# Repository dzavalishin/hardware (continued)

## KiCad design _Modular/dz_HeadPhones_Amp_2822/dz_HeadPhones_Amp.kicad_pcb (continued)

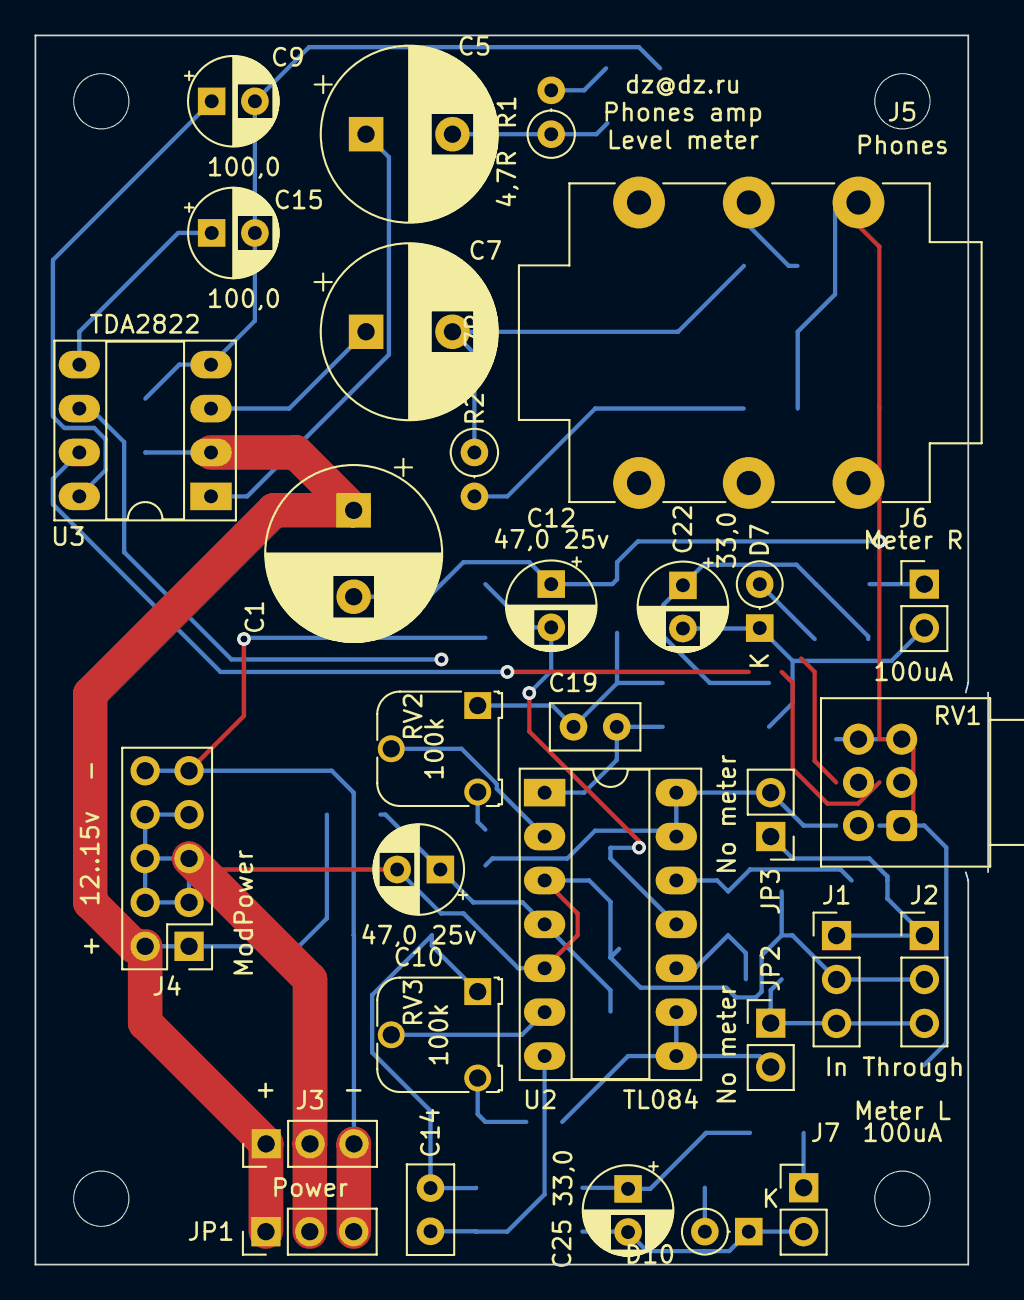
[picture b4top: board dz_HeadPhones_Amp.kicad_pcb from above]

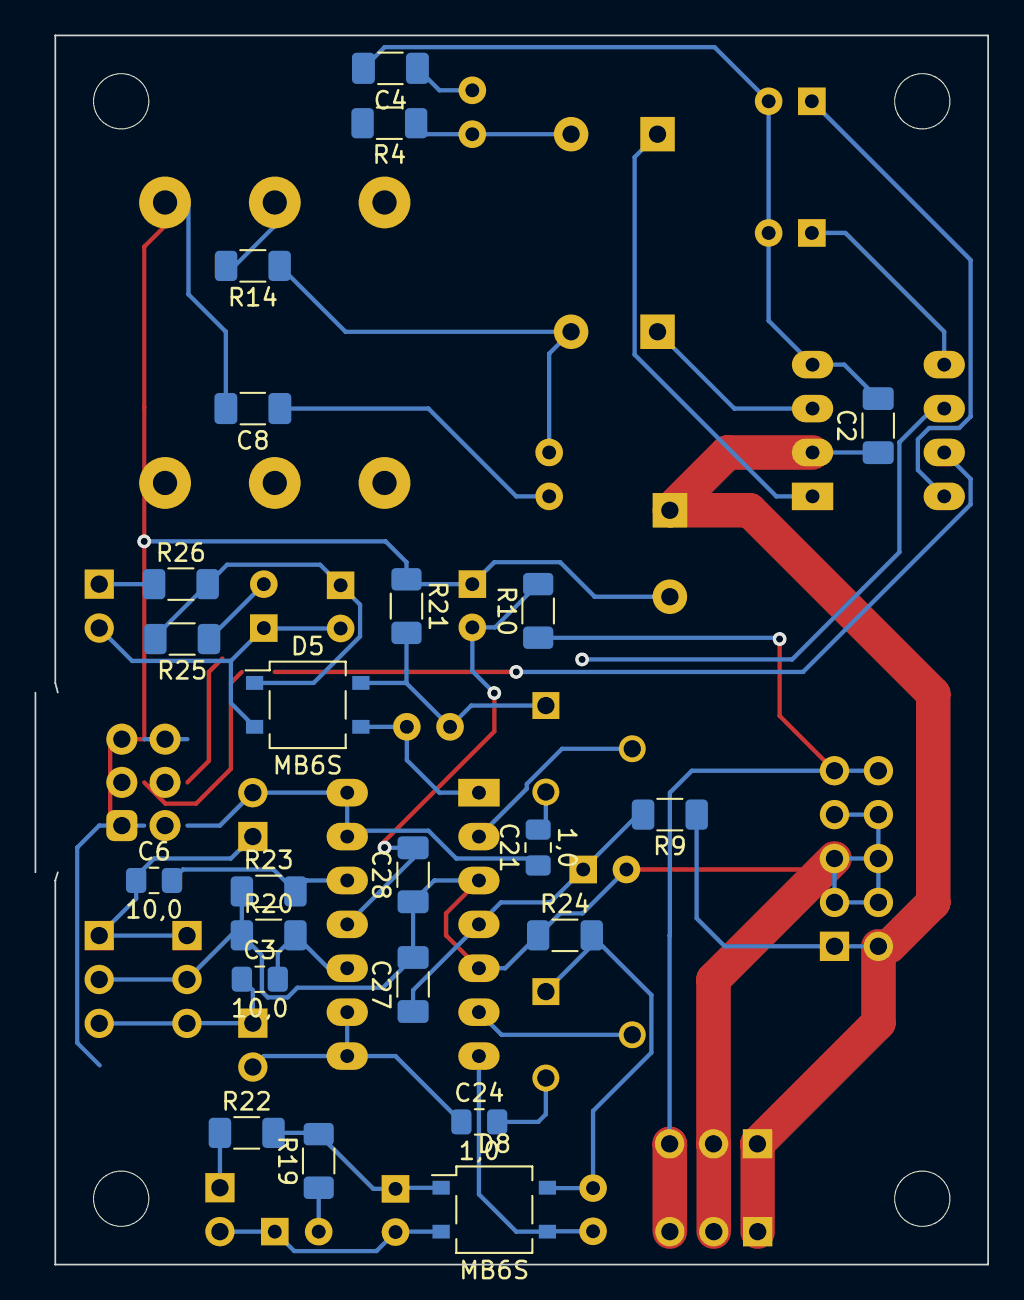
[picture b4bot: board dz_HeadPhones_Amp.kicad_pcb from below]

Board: 2 copper layers, 55.1 x 71.1 mm, 57 parts (23 on the bottom side), 39 nets.

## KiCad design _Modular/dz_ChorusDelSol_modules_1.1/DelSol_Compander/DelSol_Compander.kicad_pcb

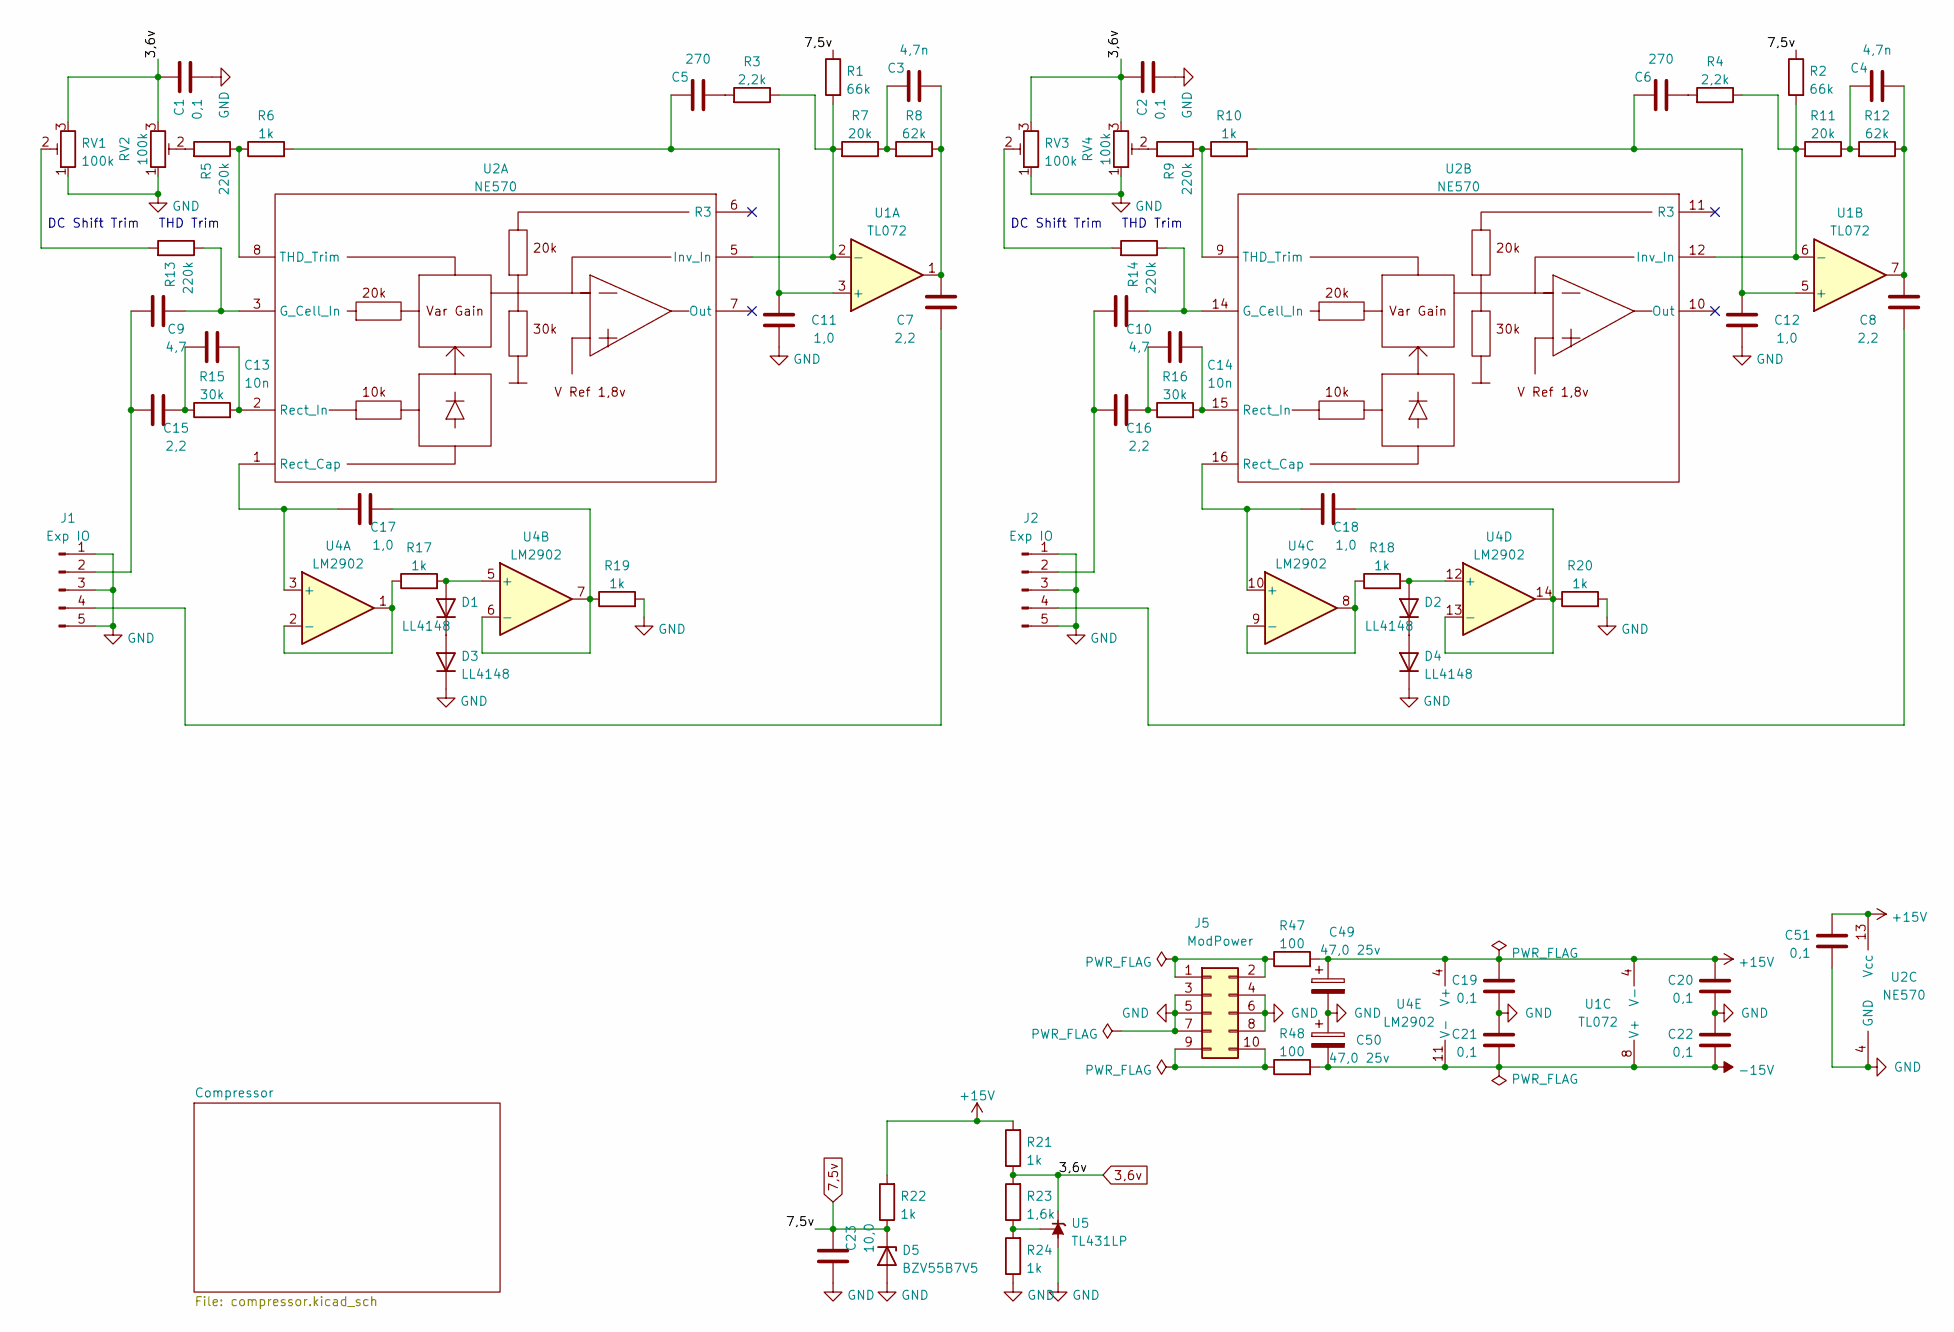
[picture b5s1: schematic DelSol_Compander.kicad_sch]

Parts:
C1, C2, C19, C20, C21, C22, C51: 0,1; C_1206_3216Metric_Pad1.33x1.80mm_HandSolder
C3, C4: 4,7n; C_0805_2012Metric_Pad1.18x1.45mm_HandSolder
C5, C6: 270; C_0805_2012Metric_Pad1.18x1.45mm_HandSolder
C7, C8, C15, C16: 2,2; C_0805_2012Metric_Pad1.18x1.45mm_HandSolder
C9, C10: 4,7; C_0805_2012Metric_Pad1.18x1.45mm_HandSolder
C11, C12, C17, C18: 1,0; C_0805_2012Metric_Pad1.18x1.45mm_HandSolder
C13, C14: 10n; C_0805_2012Metric_Pad1.18x1.45mm_HandSolder
C23: 10,0; C_0805_2012Metric_Pad1.18x1.45mm_HandSolder
C49, C50: 47,0 25v; CP_Radial_D5.0mm_P2.50mm
D1, D2, D3, D4: LL4148; D_MiniMELF
D5: BZV55B7V5; D_MiniMELF
J1, J2: Exp IO; JST_EH_B5B-EH-A_1x05_P2.50mm_Vertical
J5: ModPower; PinHeader_2x05_P2.54mm_Vertical
R1, R2: 66k; R_1206_3216Metric_Pad1.30x1.75mm_HandSolder
R3, R4: 2,2k; R_1206_3216Metric_Pad1.30x1.75mm_HandSolder
R5, R9, R13, R14: 220k; R_1206_3216Metric_Pad1.30x1.75mm_HandSolder
R6, R10, R17, R18, R19, R20, R21, R22, R24: 1k; R_1206_3216Metric_Pad1.30x1.75mm_HandSolder
R7, R11: 20k; R_1206_3216Metric_Pad1.30x1.75mm_HandSolder
R8, R12: 62k; R_1206_3216Metric_Pad1.30x1.75mm_HandSolder
R15, R16: 30k; R_1206_3216Metric_Pad1.30x1.75mm_HandSolder
R23: 1,6k; R_1206_3216Metric_Pad1.30x1.75mm_HandSolder
R47, R48: 100; R_1206_3216Metric_Pad1.30x1.75mm_HandSolder
RV1, RV2, RV3, RV4: 100k; Potentiometer_Runtron_RM-065_Vertical
U1: TL072; DIP-8_W7.62mm
U2: NE570; DIP-16_W7.62mm_Socket_LongPads
U4: LM2902; DIP-14_W7.62mm_Socket_LongPads
U5: TL431LP; TO-92_Inline

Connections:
3,6v: C1.2, C2.2, R21.1, R23.2, RV1.3, RV2.3, RV3.3, RV4.3, U5.3 (K); also elsewhere on the board
7,5v: C23.2, D5.1 (K), R1.1, R2.1, R22.1; also elsewhere on the board
+15V: C19.2, C20.2, C49.1, C51.2, R21.2, R22.2, R47.2, U1.4 (V-), U2.13 (Vcc), U4.4 (V+); also elsewhere on the board
-15V: C21.1, C22.1, C50.2, R48.2, U1.8 (V+), U4.11 (V-); also elsewhere on the board
GND: C1.1, C2.1, C11.1, C12.1, C19.1, C20.1, C21.2, C22.2, C23.1, C49.2, C50.1, C51.1, D3.1 (K), D4.1 (K), D5.2 (A), J1.1, J1.3, J1.5, J2.1, J2.3, J2.5, J5.3, J5.4, J5.5, J5.6, J5.7, J5.8, R19.2, R20.2, R24.1, RV1.1, RV2.1, RV3.1, RV4.1, U2.4 (GND), U5.2 (A); also elsewhere on the board
unnamed: C3.1, C7.2, R8.1, U1.1
unnamed: C3.2, R7.1, R8.2
unnamed: C4.1, C8.2, R12.1, U1.7
unnamed: C4.2, R11.1, R12.2
unnamed: C5.1, R3.2
unnamed: C6.1, R4.2
unnamed: C7.1, J1.4
unnamed: C8.1, J2.4
unnamed: C9.2, R13.1, U2.3 (G_Cell_In)
unnamed: C10.1, C16.1, J2.2
unnamed: C10.2, R14.1, U2.14 (G_Cell_In)
unnamed: C5.2, C11.2, R6.2, U1.3 (+)
unnamed: C6.2, C12.2, R10.2, U1.5 (+)
unnamed: C13.1, C15.2, R15.1
unnamed: C13.2, R15.2, U2.2 (Rect_In)
unnamed: C14.1, C16.2, R16.1
unnamed: C14.2, R16.2, U2.15 (Rect_In)
unnamed: C9.1, C15.1, J1.2
unnamed: C17.1, U2.1 (Rect_Cap), U4.3 (+)
unnamed: C17.2, R19.1, U4.6 (-), U4.7
unnamed: C18.1, U2.16 (Rect_Cap), U4.10 (+)
unnamed: C18.2, R20.1, U4.13 (-), U4.14
unnamed: D1.1 (K), D3.2 (A)
unnamed: D1.2 (A), R17.2, U4.5 (+)
unnamed: D2.1 (K), D4.2 (A)
unnamed: D2.2 (A), R18.2, U4.12 (+)
unnamed: J5.1, J5.2, R47.1
unnamed: J5.9, J5.10, R48.1
unnamed: R1.2, R3.1, R7.2, U1.2 (-), U2.5 (Inv_In)
unnamed: R5.1, R6.1, U2.8 (THD_Trim)
unnamed: R5.2, RV2.2
unnamed: R9.2, RV4.2
unnamed: R9.1, R10.1, U2.9 (THD_Trim)
unnamed: R2.2, R4.1, R11.2, U1.6 (-), U2.12 (Inv_In)
unnamed: R13.2, RV1.2
unnamed: R14.2, RV3.2
unnamed: R17.1, U4.1, U4.2 (-)
unnamed: R18.1, U4.8, U4.9 (-)
unnamed: R23.1, R24.2, U5.1 (REF)

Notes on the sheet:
THD Trim
DC Shift Trim

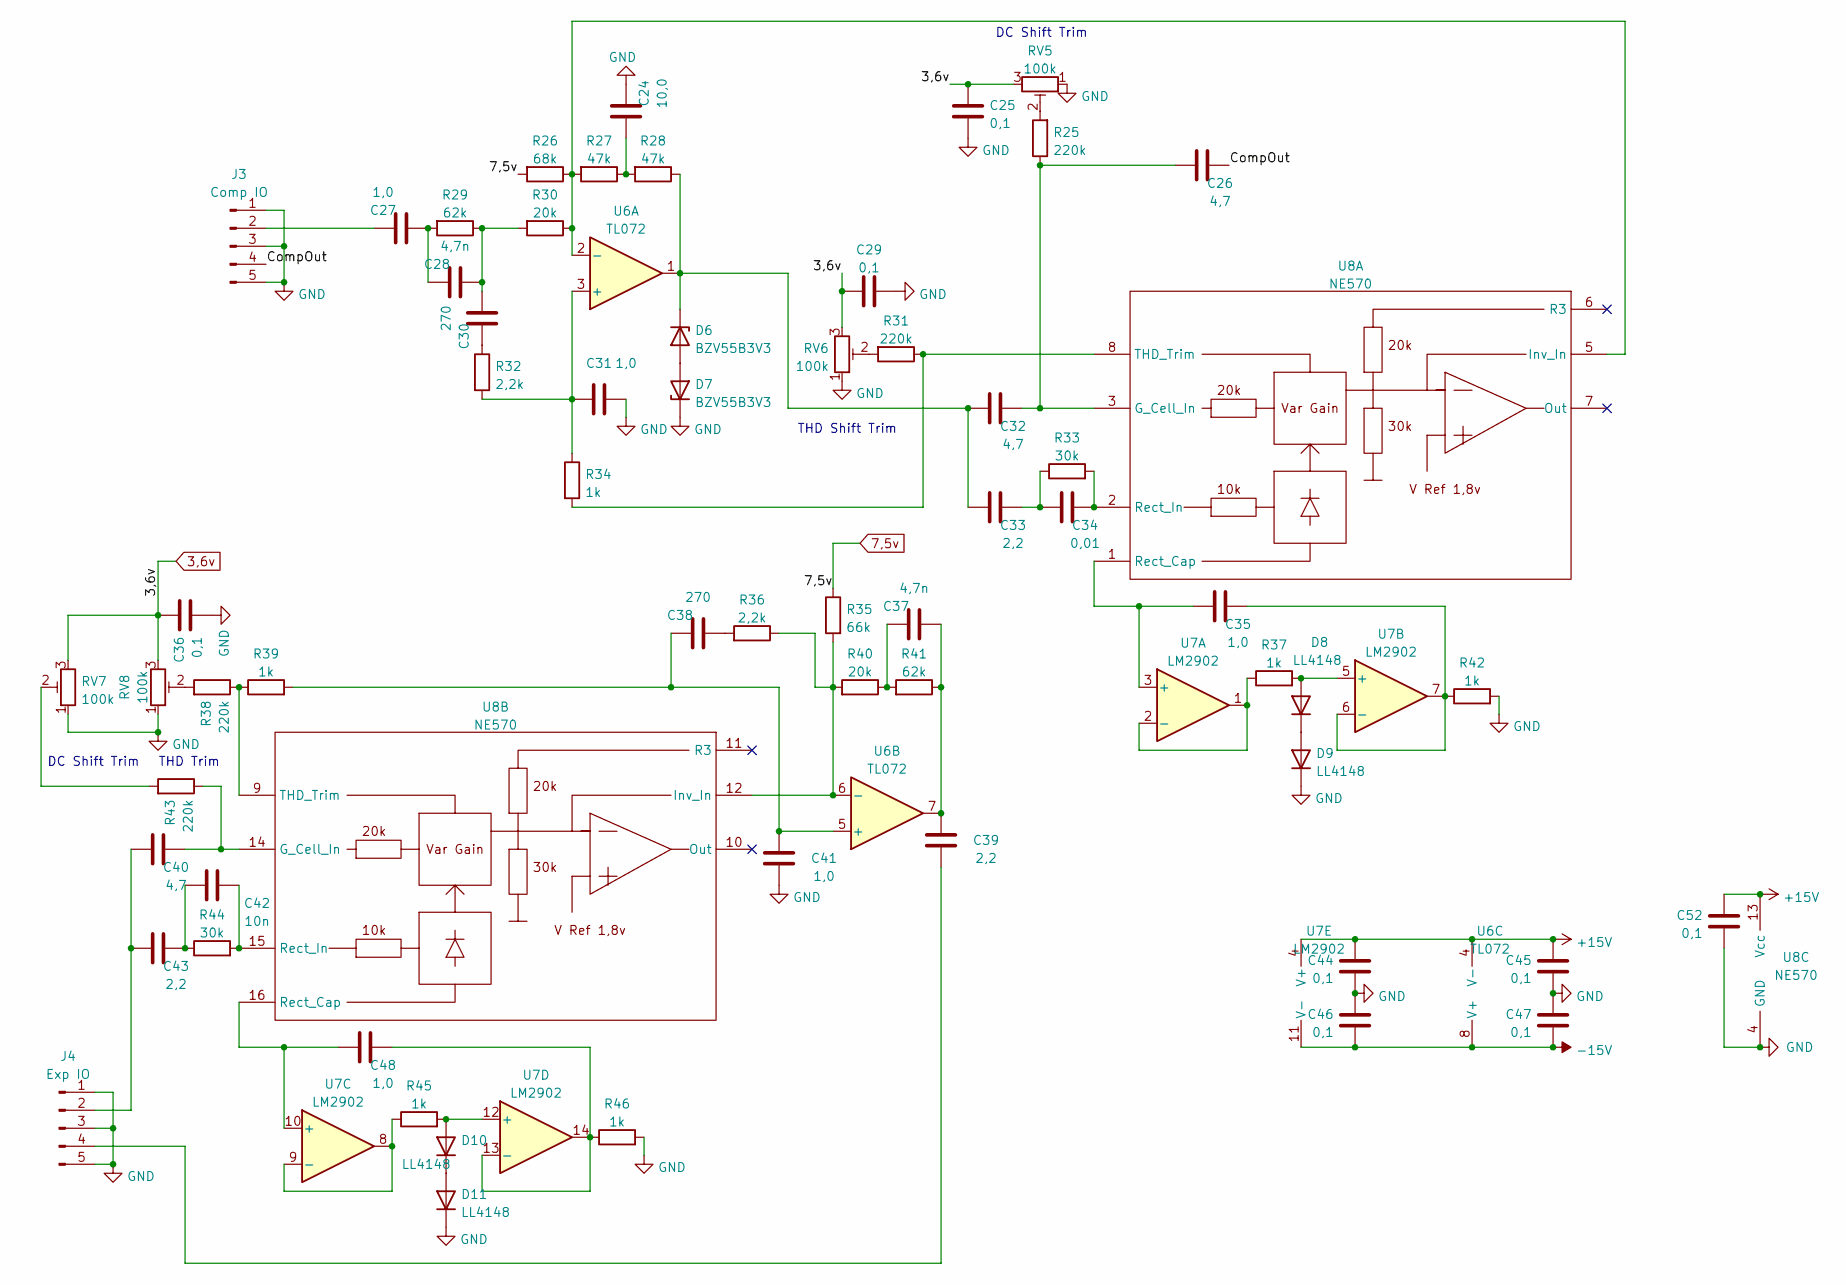
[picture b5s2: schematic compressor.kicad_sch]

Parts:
C24: 10,0; C_0805_2012Metric_Pad1.18x1.45mm_HandSolder
C25, C29, C36, C44, C45, C46, C47, C52: 0,1; C_1206_3216Metric_Pad1.33x1.80mm_HandSolder
C26, C32, C40: 4,7; C_0805_2012Metric_Pad1.18x1.45mm_HandSolder
C27, C31, C35, C41, C48: 1,0; C_0805_2012Metric_Pad1.18x1.45mm_HandSolder
C28, C37: 4,7n; C_0805_2012Metric_Pad1.18x1.45mm_HandSolder
C30, C38: 270; C_0805_2012Metric_Pad1.18x1.45mm_HandSolder
C33, C39, C43: 2,2; C_0805_2012Metric_Pad1.18x1.45mm_HandSolder
C34: 0,01; C_0805_2012Metric_Pad1.18x1.45mm_HandSolder
C42: 10n; C_0805_2012Metric_Pad1.18x1.45mm_HandSolder
D6, D7: BZV55B3V3; D_MiniMELF
D8, D9, D10, D11: LL4148; D_MiniMELF
J3: Comp IO; JST_EH_B5B-EH-A_1x05_P2.50mm_Vertical
J4: Exp IO; JST_EH_B5B-EH-A_1x05_P2.50mm_Vertical
R25, R31, R38, R43: 220k; R_1206_3216Metric_Pad1.30x1.75mm_HandSolder
R26: 68k; R_1206_3216Metric_Pad1.30x1.75mm_HandSolder
R27, R28: 47k; R_1206_3216Metric_Pad1.30x1.75mm_HandSolder
R29, R41: 62k; R_1206_3216Metric_Pad1.30x1.75mm_HandSolder
R30, R40: 20k; R_1206_3216Metric_Pad1.30x1.75mm_HandSolder
R32, R36: 2,2k; R_1206_3216Metric_Pad1.30x1.75mm_HandSolder
R33, R44: 30k; R_1206_3216Metric_Pad1.30x1.75mm_HandSolder
R34, R37, R39, R42, R45, R46: 1k; R_1206_3216Metric_Pad1.30x1.75mm_HandSolder
R35: 66k; R_1206_3216Metric_Pad1.30x1.75mm_HandSolder
RV5, RV6, RV7, RV8: 100k; Potentiometer_Runtron_RM-065_Vertical
U6: TL072; DIP-8_W7.62mm
U7: LM2902; DIP-14_W7.62mm_Socket_LongPads
U8: NE570; DIP-16_W7.62mm_Socket_LongPads

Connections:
3,6v: C25.2, C29.1, C36.2, RV5.3, RV6.3, RV7.3, RV8.3; also elsewhere on the board
7,5v: R26.2, R35.1; also elsewhere on the board
+15V: C44.2, C45.2, C52.2, U6.4 (V-), U7.4 (V+), U8.13 (Vcc); also elsewhere on the board
-15V: C46.1, C47.1, U6.8 (V+), U7.11 (V-); also elsewhere on the board
/Compressor/CompOut: C26.2, J3.4
GND: C24.2, C25.1, C29.2, C31.2, C36.1, C41.1, C44.1, C45.1, C46.2, C47.2, C52.1, D7.1 (K), D9.1 (K), D11.1 (K), J3.1, J3.3, J3.5, J4.1, J4.3, J4.5, R42.2, R46.2, RV5.1, RV6.1, RV7.1, RV8.1, U8.4 (GND); also elsewhere on the board
unnamed: C24.1, R27.1, R28.2
unnamed: C26.1, C32.2, R25.1, U8.3 (G_Cell_In)
unnamed: C27.1, C28.2, R29.2
unnamed: C27.2, J3.2
unnamed: C28.1, C30.1, R29.1, R30.2
unnamed: C30.2, R32.1
unnamed: C31.1, R32.2, R34.1, U6.3 (+)
unnamed: C32.1, C33.1, D6.1 (K), R28.1, U6.1
unnamed: C33.2, C34.1, R33.1
unnamed: C34.2, R33.2, U8.2 (Rect_In)
unnamed: C35.1, U7.3 (+), U8.1 (Rect_Cap)
unnamed: C35.2, R42.1, U7.6 (-), U7.7
unnamed: C37.1, C39.2, R41.1, U6.7
unnamed: C37.2, R40.1, R41.2
unnamed: C38.1, R36.2
unnamed: C38.2, C41.2, R39.2, U6.5 (+)
unnamed: C39.1, J4.4
unnamed: C40.1, C43.1, J4.2
unnamed: C40.2, R43.1, U8.14 (G_Cell_In)
unnamed: C42.1, C43.2, R44.1
unnamed: C42.2, R44.2, U8.15 (Rect_In)
unnamed: C48.1, U7.10 (+), U8.16 (Rect_Cap)
unnamed: C48.2, R46.1, U7.13 (-), U7.14
unnamed: D6.2 (A), D7.2 (A)
unnamed: D8.1 (K), D9.2 (A)
unnamed: D8.2 (A), R37.2, U7.5 (+)
unnamed: D10.1 (K), D11.2 (A)
unnamed: D10.2 (A), R45.2, U7.12 (+)
unnamed: R25.2, RV5.2
unnamed: R26.1, R27.2, R30.1, U6.2 (-), U8.5 (Inv_In)
unnamed: R31.1, R34.2, U8.8 (THD_Trim)
unnamed: R31.2, RV6.2
unnamed: R35.2, R36.1, R40.2, U6.6 (-), U8.12 (Inv_In)
unnamed: R37.1, U7.1, U7.2 (-)
unnamed: R38.1, R39.1, U8.9 (THD_Trim)
unnamed: R38.2, RV8.2
unnamed: R43.2, RV7.2
unnamed: R45.1, U7.8, U7.9 (-)

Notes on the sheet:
DC Shift Trim
THD Shift Trim
THD Trim

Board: 2 copper layers, 131 parts (109 on the bottom side), 83 nets, no tracks yet.

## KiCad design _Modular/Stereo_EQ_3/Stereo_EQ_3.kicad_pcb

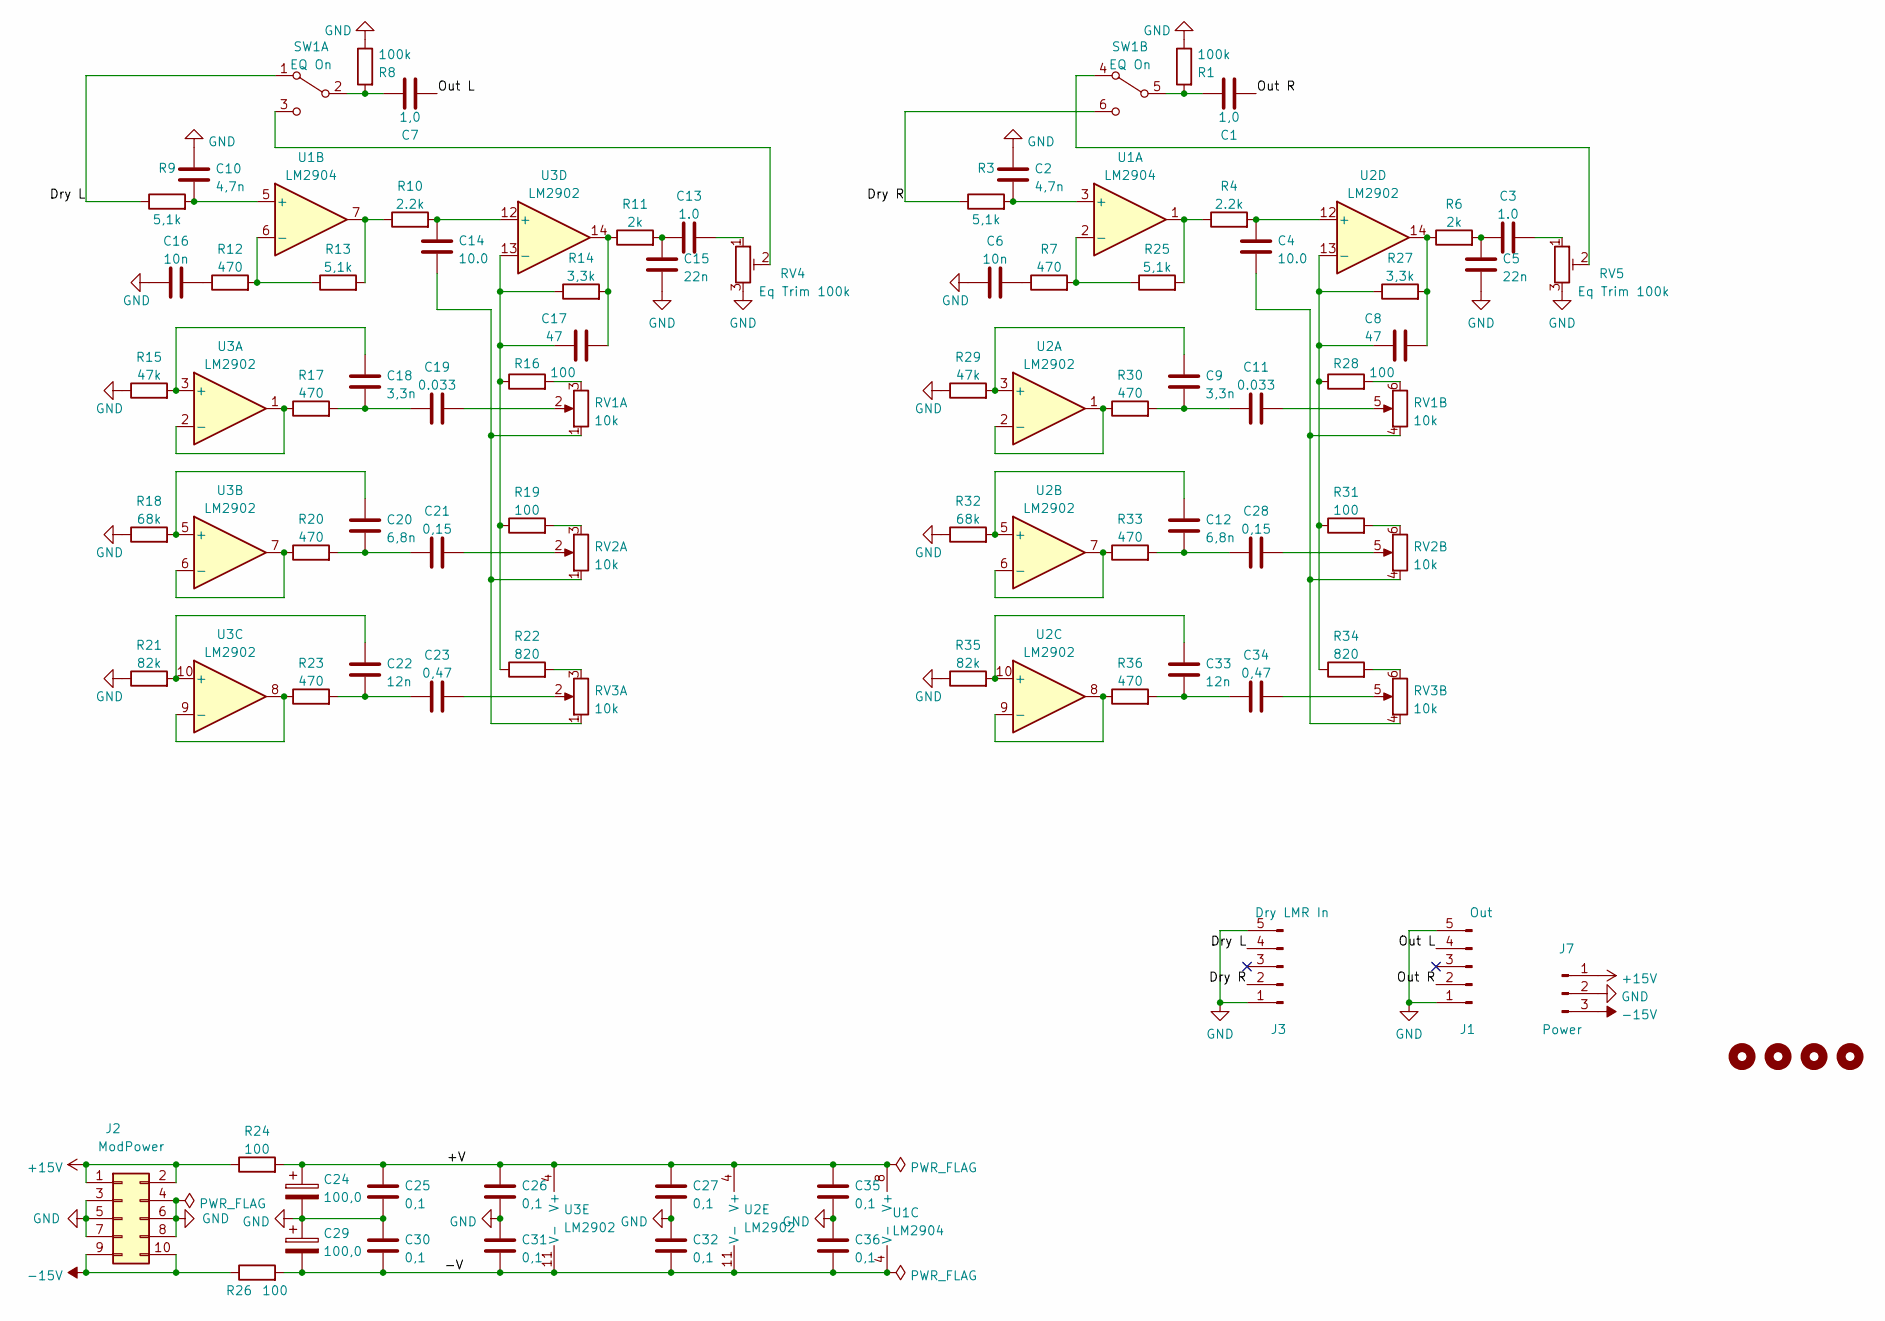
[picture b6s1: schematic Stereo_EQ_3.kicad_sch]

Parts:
C1, C7: 1,0; C_0805_2012Metric_Pad1.18x1.45mm_HandSolder
C2, C10: 4,7n; C_0805_2012Metric_Pad1.18x1.45mm_HandSolder
C3, C13: 1.0; C_0805_2012Metric_Pad1.18x1.45mm_HandSolder
C4, C14: 10.0; C_0805_2012Metric_Pad1.18x1.45mm_HandSolder
C5, C15: 22n; C_0805_2012Metric_Pad1.18x1.45mm_HandSolder
C6, C16: 10n; C_0805_2012Metric_Pad1.18x1.45mm_HandSolder
C8, C17: 47; C_0805_2012Metric_Pad1.18x1.45mm_HandSolder
C9, C18: 3,3n; C_0805_2012Metric_Pad1.18x1.45mm_HandSolder
C11, C19: 0.033; C_0805_2012Metric_Pad1.18x1.45mm_HandSolder
C12, C20: 6,8n; C_0805_2012Metric_Pad1.18x1.45mm_HandSolder
C21, C28: 0,15; C_0805_2012Metric_Pad1.18x1.45mm_HandSolder
C22, C33: 12n; C_0805_2012Metric_Pad1.18x1.45mm_HandSolder
C23, C34: 0,47; C_0805_2012Metric_Pad1.18x1.45mm_HandSolder
C24, C29: 100,0; C_Elec_6.3x5.8
C25, C26, C27, C30, C31, C32, C35, C36: 0,1; C_1206_3216Metric_Pad1.33x1.80mm_HandSolder
H1, H2, H3, H4: MountingHole; MountingHole_3.2mm_M3
J1: Out; JST_XH_B5B-XH-AM_1x05_P2.50mm_Vertical
J2: ModPower; PinHeader_2x05_P2.54mm_Vertical
J3: Dry LMR In; JST_XH_B5B-XH-AM_1x05_P2.50mm_Vertical
J7: Power; PinHeader_1x03_P2.54mm_Vertical
R1, R8: 100k; R_1206_3216Metric_Pad1.30x1.75mm_HandSolder
R3, R9, R13, R25: 5,1k; R_1206_3216Metric_Pad1.30x1.75mm_HandSolder
R4, R10: 2.2k; R_1206_3216Metric_Pad1.30x1.75mm_HandSolder
R6, R11: 2k; R_1206_3216Metric_Pad1.30x1.75mm_HandSolder
R7, R12, R17, R20, R23, R30, R33, R36: 470; R_1206_3216Metric_Pad1.30x1.75mm_HandSolder
R14, R27: 3,3k; R_1206_3216Metric_Pad1.30x1.75mm_HandSolder
R15, R29: 47k; R_1206_3216Metric_Pad1.30x1.75mm_HandSolder
R16, R19, R24, R26, R28, R31: 100; R_1206_3216Metric_Pad1.30x1.75mm_HandSolder
R18, R32: 68k; R_1206_3216Metric_Pad1.30x1.75mm_HandSolder
R21, R35: 82k; R_1206_3216Metric_Pad1.30x1.75mm_HandSolder
R22, R34: 820; R_1206_3216Metric_Pad1.30x1.75mm_HandSolder
RV1, RV2, RV3: 10k; Potentiometer_Alps_RK097_Dual_Horizontal
RV4, RV5: Eq Trim 100k; Potentiometer_Runtron_RM-065_Vertical
SW1: EQ On; SW_NKK_G1xJP
U1: LM2904; DIP-8_W7.62mm
U2, U3: LM2902; DIP-14_W7.62mm

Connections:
+15V: J2.1, J2.2, J7.1, R24.1
-15V: J2.9, J2.10, J7.3, R26.1
/+V: C24.1, C25.1, C26.1, C27.1, C35.1, R24.2, U1.8 (V+), U2.4 (V+), U3.4 (V+)
/-V: C29.2, C30.2, C31.2, C32.2, C36.2, R26.2, U1.4 (V-), U2.11 (V-), U3.11 (V-)
/Dry L: J3.4, R9.1, SW1.1 (A)
/Dry R: J3.2, R3.1, SW1.6 (C)
/Out L: C7.2, J1.4
/Out R: C1.2, J1.2
GND: C2.1, C5.2, C6.1, C10.1, C15.2, C16.1, C24.2, C25.2, C26.2, C27.2, C29.1, C30.1, C31.1, C32.1, C35.2, C36.1, J1.1, J1.5, J2.3, J2.4, J2.5, J2.6, J2.7, J2.8, J3.1, J3.5, J7.2, R1.1, R8.1, R15.1, R18.1, R21.1, R29.1, R32.1, R35.1, RV4.3, RV5.3
unnamed: C1.1, R1.2, SW1.5 (B)
unnamed: C3.1, RV5.1
unnamed: C3.2, C5.1, R6.2
unnamed: C4.2, R4.2, U2.12 (+)
unnamed: C6.2, R7.1
unnamed: C7.1, R8.2, SW1.2 (B)
unnamed: C8.1, R27.1, R28.1, R31.1, R34.1, U2.13 (-)
unnamed: C8.2, R6.1, R27.2, U2.14
unnamed: C9.1, R29.2, U2.3 (+)
unnamed: C10.2, R9.2, U1.5 (+)
unnamed: C9.2, C11.1, R30.2
unnamed: C12.1, R32.2, U2.5 (+)
unnamed: C12.2, C28.1, R33.2
unnamed: C13.1, RV4.1
unnamed: C13.2, C15.1, R11.2
unnamed: C14.1, RV1.1, RV2.1, RV3.1
unnamed: C14.2, R10.2, U3.12 (+)
unnamed: C16.2, R12.1
unnamed: C17.1, R14.1, R16.1, R19.1, R22.1, U3.13 (-)
unnamed: C17.2, R11.1, R14.2, U3.14
unnamed: C18.1, R15.2, U3.3 (+)
unnamed: C18.2, C19.1, R17.2
unnamed: C19.2, RV1.2
unnamed: C20.1, R18.2, U3.5 (+)
unnamed: C20.2, C21.1, R20.2
unnamed: C21.2, RV2.2
unnamed: C22.1, R21.2, U3.10 (+)
unnamed: C22.2, C23.1, R23.2
unnamed: C23.2, RV3.2
unnamed: C33.1, R35.2, U2.10 (+)
unnamed: C33.2, C34.1, R36.2
unnamed: R10.1, R13.2, U1.7
unnamed: R12.2, R13.1, U1.6 (-)
unnamed: R16.2, RV1.3
unnamed: R17.1, U3.1, U3.2 (-)
unnamed: R19.2, RV2.3
unnamed: R20.1, U3.6 (-), U3.7
unnamed: R22.2, RV3.3
unnamed: R23.1, U3.8, U3.9 (-)
unnamed: R30.1, U2.1, U2.2 (-)
unnamed: R33.1, U2.6 (-), U2.7
unnamed: R36.1, U2.8, U2.9 (-)
unnamed: C4.1, RV1.4, RV2.4, RV3.4
unnamed: C11.2, RV1.5
unnamed: R28.2, RV1.6
unnamed: C28.2, RV2.5
unnamed: R31.2, RV2.6
unnamed: C34.2, RV3.5
unnamed: R34.2, RV3.6
unnamed: RV4.2, SW1.3 (C)
unnamed: RV5.2, SW1.4 (A)
unnamed: R4.1, R25.2, U1.1
unnamed: R7.2, R25.1, U1.2 (-)
unnamed: C2.2, R3.2, U1.3 (+)

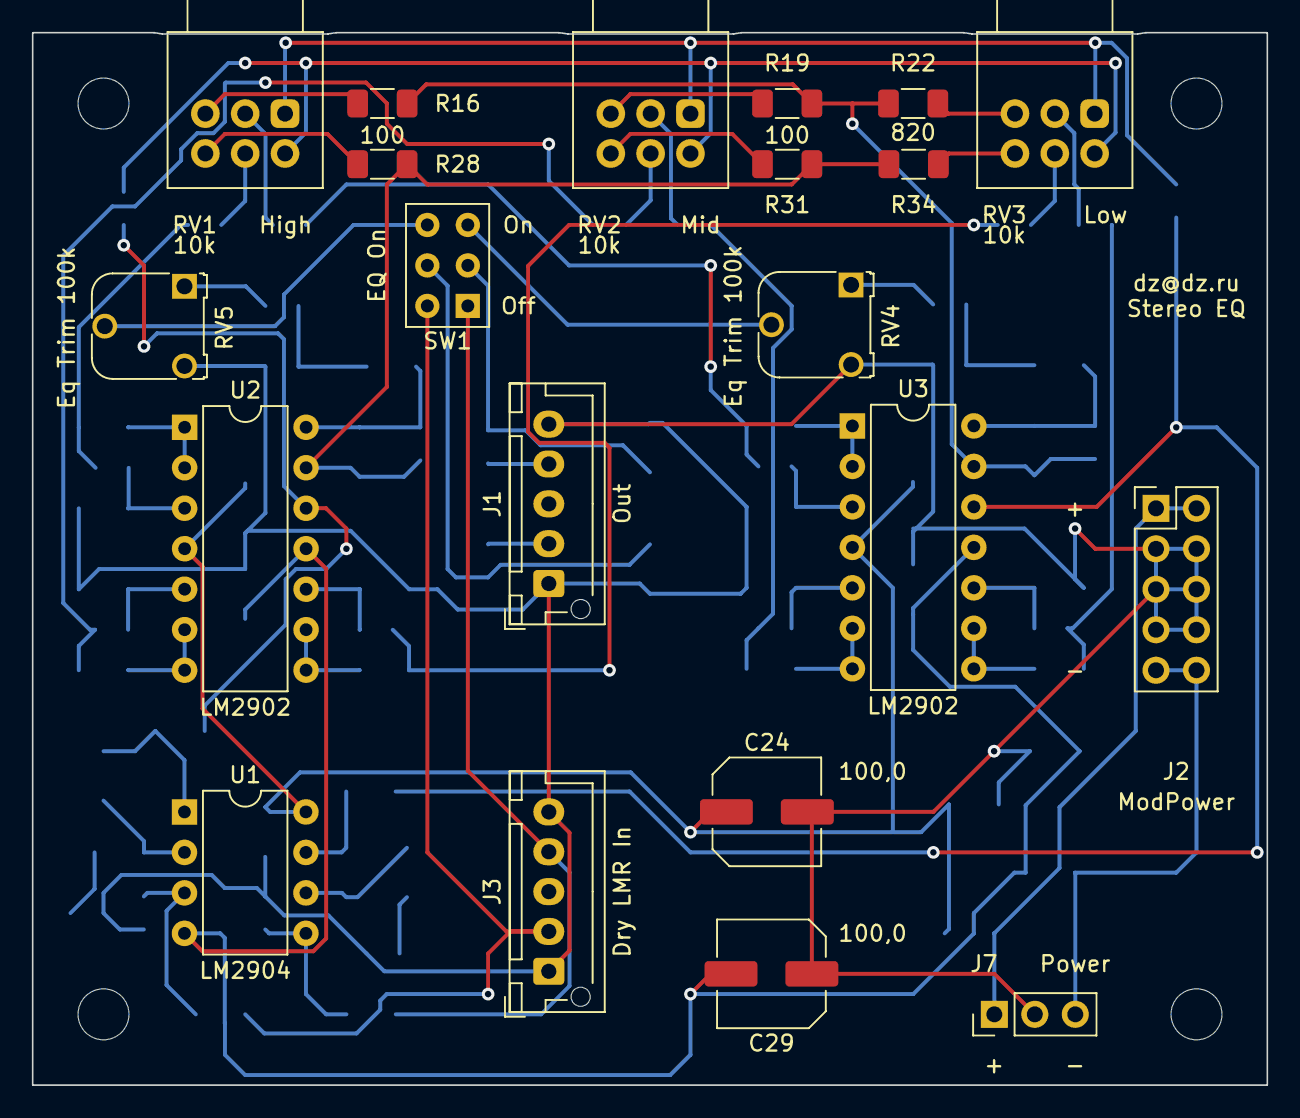
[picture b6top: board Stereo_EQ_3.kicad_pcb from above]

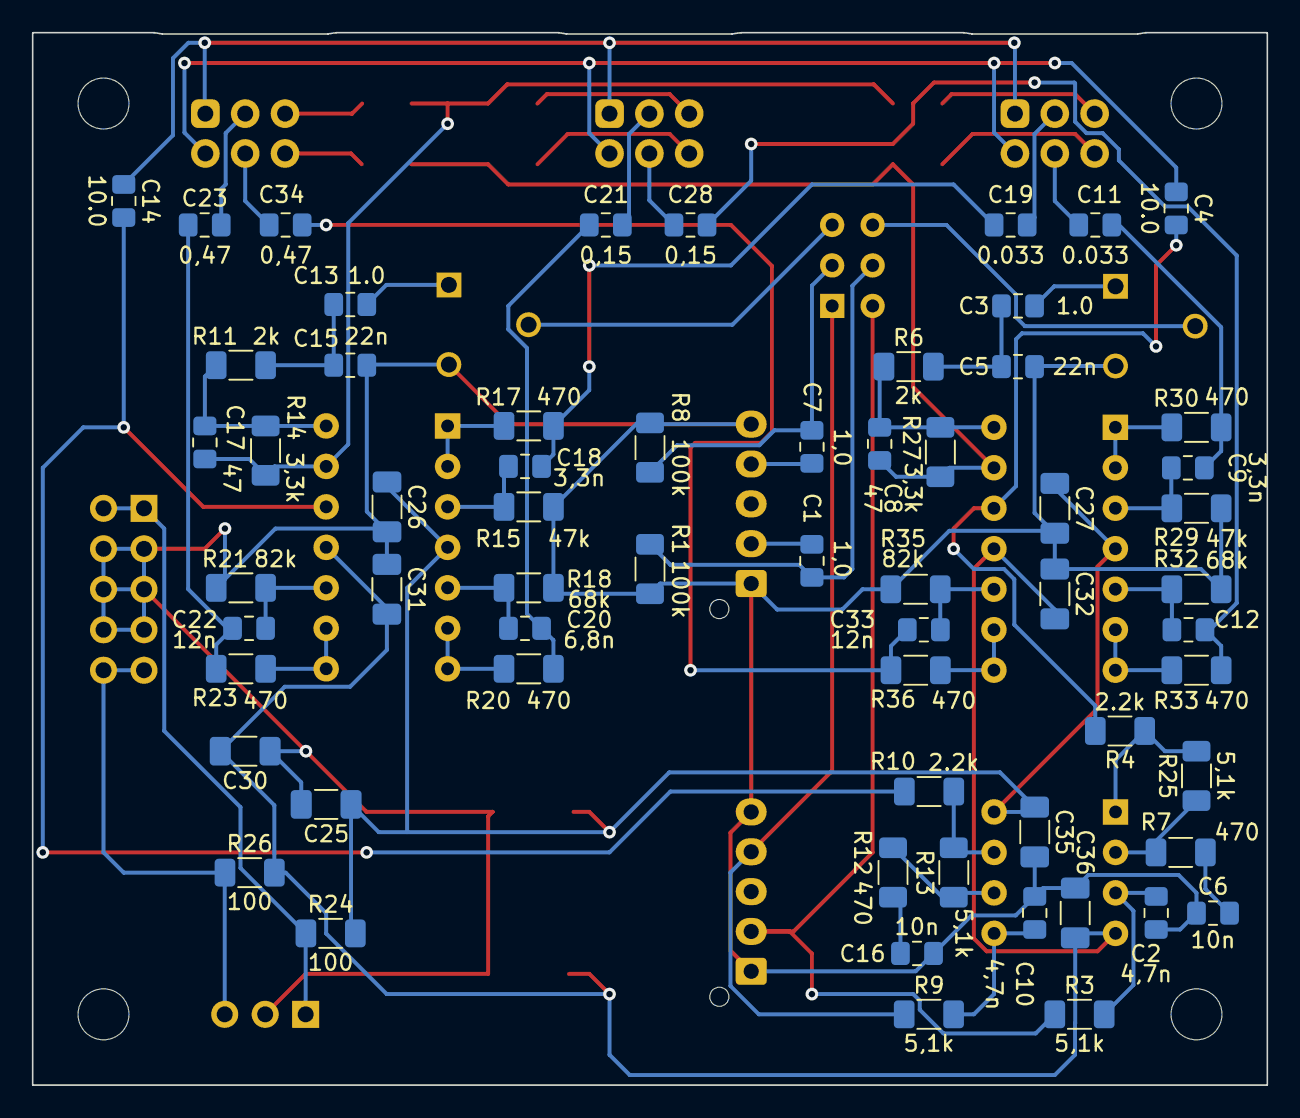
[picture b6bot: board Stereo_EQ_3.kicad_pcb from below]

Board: 2 copper layers, 77.5 x 66.0 mm, 87 parts (62 on the bottom side), 63 nets.

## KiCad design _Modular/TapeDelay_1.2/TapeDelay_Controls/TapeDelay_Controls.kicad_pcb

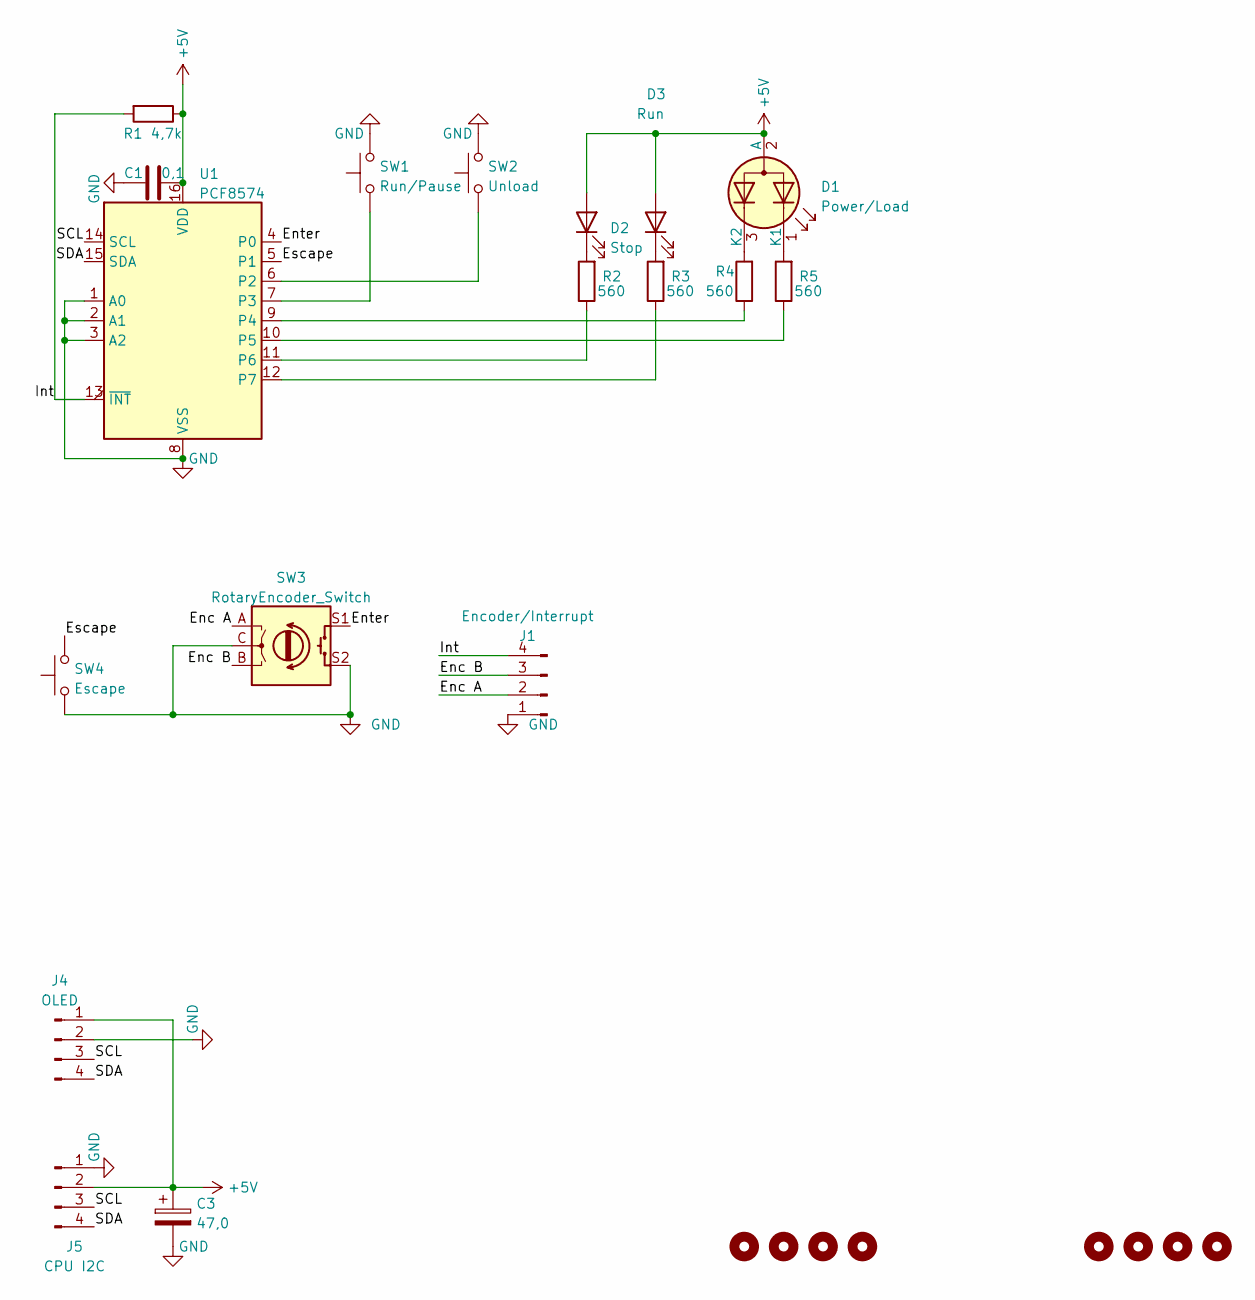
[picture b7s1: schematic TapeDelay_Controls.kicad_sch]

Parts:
C1: 0,1; C_1206_3216Metric_Pad1.33x1.80mm_HandSolder
C3: 47,0; CP_Radial_D6.3mm_P2.50mm
D1: Power/Load; LED_D3.0mm-3
D2: Stop; LED_D3.0mm
D3: Run; LED_D3.0mm
H1, H2, H3, H4, H5, H6, H7, H8: MountingHole; MountingHole_3.2mm_M3
J1: Encoder/Interrupt; PinHeader_1x04_P2.54mm_Vertical
J4: OLED; PinHeader_1x04_P2.54mm_Vertical
J5: CPU I2C; PinHeader_1x04_P2.54mm_Vertical
R1: 4,7k; R_1206_3216Metric_Pad1.30x1.75mm_HandSolder
R2, R3, R4, R5: 560; R_1206_3216Metric_Pad1.30x1.75mm_HandSolder
SW1: Run/Pause; SW_PUSH_6mm
SW2: Unload; SW_PUSH_6mm
SW3: RotaryEncoder_Switch; RotaryEncoder_Bourns_Vertical_PEC12R-3xxxF-Sxxxx
SW4: Escape; SW_PUSH_6mm
U1: PCF8574; DIP-16_W7.62mm_Socket_LongPads

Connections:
+5V: C1.2, C3.1, D1.2 (A), D2.2 (A), D3.2 (A), J4.1, J5.2, R1.1, U1.16 (VDD)
/Enc A: J1.2, SW3.A
/Enc B: J1.3, SW3.B
/Enter: SW3.S1, U1.4 (P0)
/Escape: SW4.2, U1.5 (P1)
/Int: J1.4, R1.2, U1.13 (~INT)
/SCL: J4.3, J5.3, U1.14 (SCL)
/SDA: J4.4, J5.4, U1.15 (SDA)
GND: C1.1, C3.2, J1.1, J4.2, J5.1, SW1.1, SW2.1, SW3.C, SW3.S2, SW4.1, U1.1 (A0), U1.2 (A1), U1.3 (A2), U1.8 (VSS)
unnamed: D1.1 (K1), R5.2
unnamed: D1.3 (K2), R4.2
unnamed: D2.1 (K), R2.2
unnamed: D3.1 (K), R3.2
unnamed: R2.1, U1.11 (P6)
unnamed: R3.1, U1.12 (P7)
unnamed: R4.1, U1.9 (P4)
unnamed: R5.1, U1.10 (P5)
unnamed: SW1.2, U1.7 (P3)
unnamed: SW2.2, U1.6 (P2)
